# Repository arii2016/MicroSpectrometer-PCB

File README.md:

MicroSpectrometer-PCB
=================

マイクロ分光器のPCBになります。
以下のサイトを参考にして作成いたしました。<br/ >
http://www.tricorderproject.org/blog/sneak-peek-3d-printable-mini-spectrometer/
<br/ >
ラインセンサーにはTSL1401CLを使用します。また、TSL1401CLのアナログ信号をADコンバーターAD7940に入力し、SPI通信でデータを取得します。

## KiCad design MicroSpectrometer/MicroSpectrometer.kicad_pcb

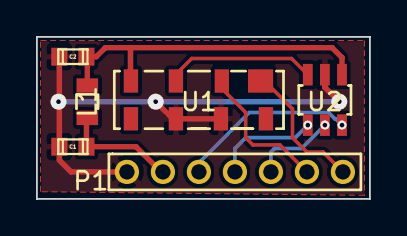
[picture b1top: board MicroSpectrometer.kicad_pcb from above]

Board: 2 copper layers, 18.5 x 9.0 mm, 6 parts (0 on the bottom side), 9 nets.

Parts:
C1, C2: C; c_0603
L1: INDUCTOR; MLF2012
P1: CONN_7; 292132-7
U1: TSL1401CL
U2: AD7940

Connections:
DGND: C1.2, C2.2, P1.1, U1.6, U1.7, U2.2
unnamed: U1.3, U2.3
unnamed: P1.6, U1.2
unnamed: P1.7, U1.1
unnamed: P1.4, U2.4
unnamed: P1.3, U2.6
unnamed: P1.5, U2.5
unnamed: C2.1, L1.2, U1.4, U2.1
VDD: C1.1, L1.1, P1.2

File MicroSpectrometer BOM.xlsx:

| Part / Value | Package | Manufacturer | Part No | Circuit Reference | Qty
 | TSL1401CL | CL | Austriamicrosystems | TSL1401CL | U1 | 1
 | AD7940 | SOT-23 | Analog Devices | AD7940BRJZ-REEL7 | U2 | 1
 | 100uH | 2012 | TDK | MLF2012C101K | L1 | 1
 | 0.022uF | 0603 | Any | Any | C1,C2 | 2
 | CONN7 |  | TE Connectivity | 292132-7 | P1 | 1

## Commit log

2016-08-19 :tada: Added .gitattributes
